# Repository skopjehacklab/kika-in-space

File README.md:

# kika-in-space
A baloon project

## Electronics Description

AVR µC collects data from sensors and GPS module (uart rx) and sends it out to a modem and TX1/HX1 radio module (via uart
tx). Data is sent in the [NMEA](http://www.catb.org/gpsd/NMEA.html) format.

Sensors:
* Temperature 3x DS18B20 (1-Wire)
* Pressure BMP085 (I²C)
* Humidity DHT22 (proprietary 1-Wire)
* Accelerometer + Gyroscope MPU-6050 (I²C)
* GPS module (uart)

## BOM
...

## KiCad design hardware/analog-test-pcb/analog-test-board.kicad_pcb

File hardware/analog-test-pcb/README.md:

Requirement:
The input to the HX1 module needs a swing from 0 to 5V in order to achive the ±5kHz deviation (typical specs from the datasheet).

Problem:
The output of the DS8500 is 500mVpp (typ) with a 1.5V of DC offset. The maximum load at the ouput is 30kOHM (by specs in the datasheet). This needs to be analogly processed in order to fit the signal level required by the HX1 module

Solution:
Do some analog processing!

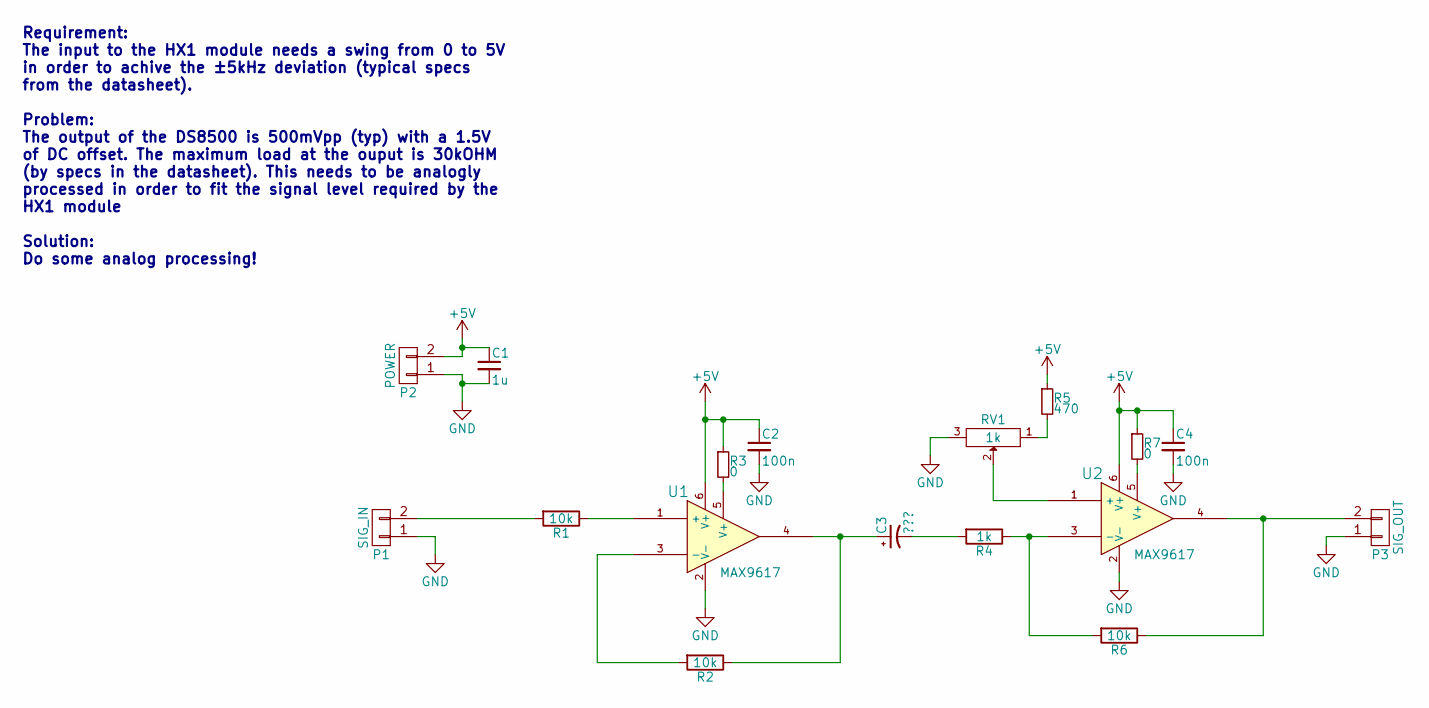
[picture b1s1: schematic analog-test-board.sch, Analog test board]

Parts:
C1: 1u
C2, C4: 100n
C3: ???
P1: SIG_IN
P2: POWER
P3: SIG_OUT
R1, R2, R6: 10k
R3, R7: 0
R4: 1k
R5: 470
RV1: 1k
U1, U2: MAX9617

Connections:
+5V: C1.1, C2.1, C4.1, P2.2, R3.1, R5.1, R7.1, U1.6 (V+), U2.6 (V+)
GND: C1.2, C2.2, C4.2, P1.1, P2.1, P3.1, RV1.3, U1.2 (V-), U2.2 (V-)
unnamed: C3.1, R2.1, U1.4
unnamed: C3.2, R4.2
unnamed: P1.2, R1.2
unnamed: P3.2, R6.1, U2.4
unnamed: R1.1, U1.1 (+)
unnamed: R2.2, U1.3 (-)
unnamed: R3.2, U1.5 (V+)
unnamed: R4.1, R6.2, U2.3 (-)
unnamed: R5.2, RV1.1
unnamed: R7.2, U2.5 (V+)
unnamed: RV1.2, U2.1 (+)

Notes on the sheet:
Requirement: The input to the HX1 module needs a swing from 0 to 5V in order to achive the ±5kHz deviation (typical specs from the datasheet). Problem: The output of the DS8500 is 500mVpp (typ) with a 1.5V of DC offset. The maximum load at the ouput is 30kOHM (by specs in the datasheet). This needs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

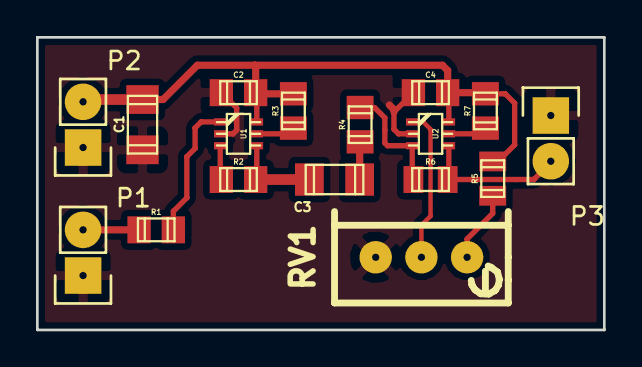
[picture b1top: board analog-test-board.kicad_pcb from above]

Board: 2 copper layers, 31.5 x 16.3 mm, 17 parts (0 on the bottom side), 13 nets.

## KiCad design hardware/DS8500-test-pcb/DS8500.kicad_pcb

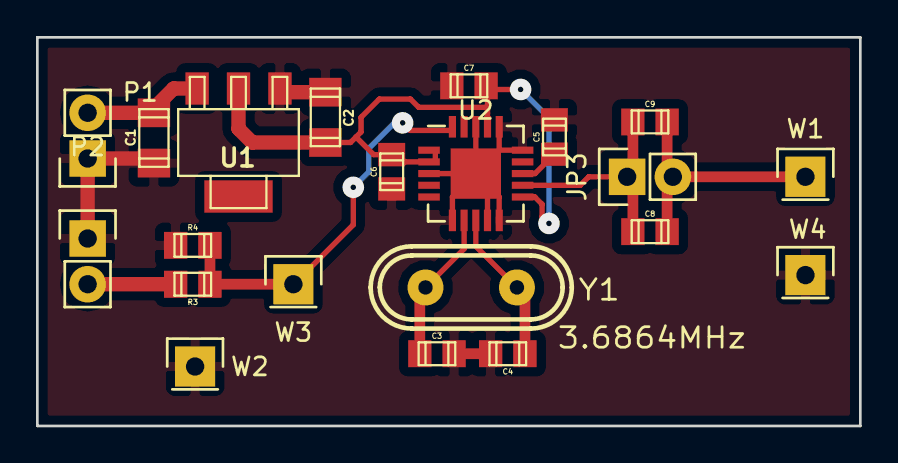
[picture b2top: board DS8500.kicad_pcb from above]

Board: 2 copper layers, 45.7 x 21.6 mm, 21 parts (0 on the bottom side), 10 nets.

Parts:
C1, C2: 1u; c_1206
C3, C4: 22p; c_0805
C5, C6, C7, C8, C9: 100n; c_0805
JP3: Pin_Header_Straight_1x02
P1: POWER; Pin_Header_Straight_1x02
P2: INTERFACE; Pin_Header_Straight_1x02
R3: 10k; r_0805
R4: 20k; r_0805
U1: AP1117V5; sot223
U2: DS8500; QFN-20-1EP_5x5mm_Pitch0.65mm
W1: FSK_OUT; Pin_Header_Straight_1x01
W2, W4: GND; Pin_Header_Straight_1x01
W3: FSK_IN; Pin_Header_Straight_1x01
Y1: 3.6864MHz; crystal_hc-49u

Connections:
+5V: C1.1, P1.2, U1.3
GND: C1.2, C2.2, C3.1, C4.1, C5.1, C6.2, C7.2, P1.1, P2.1, R4.2, U1.1, U2.3, U2.6, U2.9, U2.10, U2.15, U2.16, U2.18, U2.21, W2.1, W4.1
unnamed: C3.2, U2.7, Y1.2
unnamed: C4.2, U2.8, Y1.1
unnamed: C5.2, U2.13
unnamed: C8.1, C9.1, JP3.2, W1.1
unnamed: C8.2, C9.2, JP3.1, U2.12
unnamed: P2.2, R3.1
unnamed: R3.2, R4.1, U2.20, W3.1
VCC: C2.1, C6.1, C7.1, U1.2, U2.1, U2.2, U2.11, U2.17

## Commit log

2016-04-25 import hello_uart_async from tuupola/avr_demo
    https://github.com/tuupola/avr_demo
2016-04-25 don't send \r automatically
2016-04-25 return EOF when rx buffer empty
2016-04-25 blink without delay_ms
    but still blink from the main loop so that we know it rolls.
    had to implement crude millis for that, using timer0
2016-04-25 uart sends what's received
    rx is from the GPS module, tx goes to the TX1 module
2016-04-25 separate millis() implementation
    and better, 64x prescaller, OCR0A set to 250 = 1ms
2016-04-25 try to fix off-by-one in send isr
2016-04-25 Added the apropriate usb port and baudrate for Arduino UNO
2016-04-25 getchar (which is a link to fgetc) returns int, not char
2016-04-25 rx and tx buffer should be char, not int
2016-04-25 try to fix off-by-one in rx
2016-04-25 The RX interrupt needs to be enabled
2016-04-25 Hello World\!\r
2016-04-26 nothing exceptional
    LED instead of PORTB5, call millis() only once in the main loop
2016-04-26 sensors in readme
2016-04-26 fix md links and spelling
2016-04-26 Initial commit. A test PCB for the DS8500 HART modem, which incorporates a FSK 1200baud modem
2016-04-26 we can use TX1 or HX1 radio module
2016-04-26 First revision of the DS8500 schematic
2016-04-26 Schematic in PDF form
2016-04-26 ignore .bak files generated from KiCAD
2016-04-26 Associated the appropriate footprints to the components
2016-04-26 Updated the PDF
2016-04-26 No need for the .bak file
2016-04-26 ignore avr-gcc artefacts too
2016-04-29 Added extra test points at the input
2016-04-29 Ignore the *.kicad_pcb-bak file
2016-04-29 Initial PCB import
2016-04-29 PCB - WIP
2016-04-29 No need for RTS. We will be always in MODULATOR mode -> RTS pin tied to GND
2016-04-29 0-OHM jumper resistor
2016-04-29 Beta(?) version of the PCB
2016-04-30 Ignore dolphin .directory files
2016-04-30 Some minor changes to the flood fill
2016-04-30 Wrong package for DS8500. The correct one is TQFN-20 5x5mm
2016-04-30 Extended the leads of the TQFN-20 for hand soldering
2016-04-30 One more extension of the leads
2016-04-30 Minor changes
2016-05-04 Updated the schematics PDF file
2016-05-04 Initial commit with the README explainig the board
2016-05-04 Typo.
2016-05-08 The schematic. A buffer followed by a inverting amp with a DC offset
2016-05-08 The cache library
2016-05-08 First version of the pcb
2016-05-08 PDF version of the schematic
2016-05-08 Minor change
2016-05-08 Final version
2016-05-08 The motherboard
